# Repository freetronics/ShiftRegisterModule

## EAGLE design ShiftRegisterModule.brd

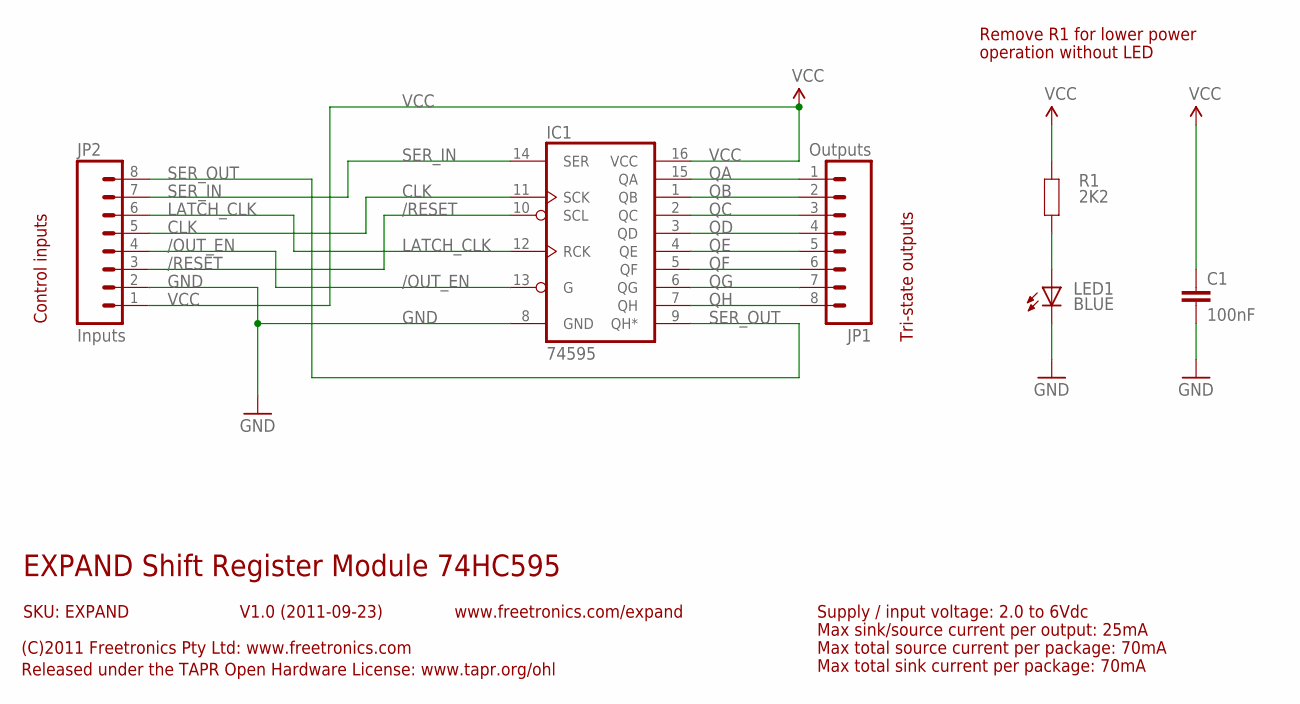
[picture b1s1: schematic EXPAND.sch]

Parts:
C1: 100nF; 0603
IC1: 74595; TSSOP16
JP1: Outputs; 1X08
JP2: Inputs; 1X08
LED1: BLUE; LED-0603
R1: 2K2; 0603

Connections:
/OUT_EN: IC1.13 (G), JP2.4
/RESET: IC1.10 (SCL), JP2.3
CLK: IC1.11 (SCK), JP2.5
GND: C1.2, IC1.8 (GND), JP2.2, LED1.C
LATCH_CLK: IC1.12 (RCK), JP2.6
unnamed: LED1.A, R1.1
QA: IC1.15 (QA), JP1.1
QB: IC1.1 (QB), JP1.2
QC: IC1.2 (QC), JP1.3
QD: IC1.3 (QD), JP1.4
QE: IC1.4 (QE), JP1.5
QF: IC1.5 (QF), JP1.6
QG: IC1.6 (QG), JP1.7
QH: IC1.7 (QH), JP1.8
SER_IN: IC1.14 (SER), JP2.7
SER_OUT: IC1.9 (QH*), JP2.8
VCC: C1.1, IC1.16 (VCC), JP2.1, R1.2

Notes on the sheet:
EXPAND Shift Register Module 74HC595
V1.0 (2011-09-23)
SKU: EXPAND
(C)2011 Freetronics Pty Ltd: www.freetronics.com
Released under the TAPR Open Hardware License: www.tapr.org/ohl
www.freetronics.com/expand
Supply / input voltage: 2.0 to 6Vdc
Max sink/source current per output: 25mA
Remove R1 for lower power
operation without LED
Max total source current per package: 70mA
Max total sink current per package: 70mA
Control inputs
Tri-state outputs

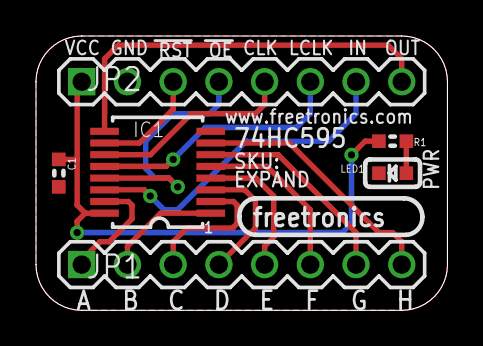
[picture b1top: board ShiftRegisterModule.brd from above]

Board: 2 copper layers, 22.9 x 15.2 mm, 6 parts (0 on the bottom side), 17 nets.

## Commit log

2011-09-24 Initial project import
2011-09-24 Renamed project files
2011-09-24 Routing, overlay, and schematic tweaks
2011-09-27 Changed LED current limiter to 1K5
2011-09-27 Added 100nF bypass cap
2011-09-30 v1.0 released, also with pdf
2011-12-12 Schematic and Reference PDF renamed
2019-04-24 Improved designators
2019-04-24 Mode board and schematic consistent
2019-07-01 Renamed project files to match SKU
